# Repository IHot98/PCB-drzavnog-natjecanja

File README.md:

PCB drzavnog natjecanja
---
Za zadatak natjecanja bilo je potrebno izraditi robota (programranje, 3D dizajn i PCB)

Moj zadatak je bilo crtanje PCB-a i ovo je rezultat toga
 
 Za crtanje PCB-a bilo je zadana shema i ograničenja / dimenzije same pločice te koje se komponente moraju koristiti (kućišta)

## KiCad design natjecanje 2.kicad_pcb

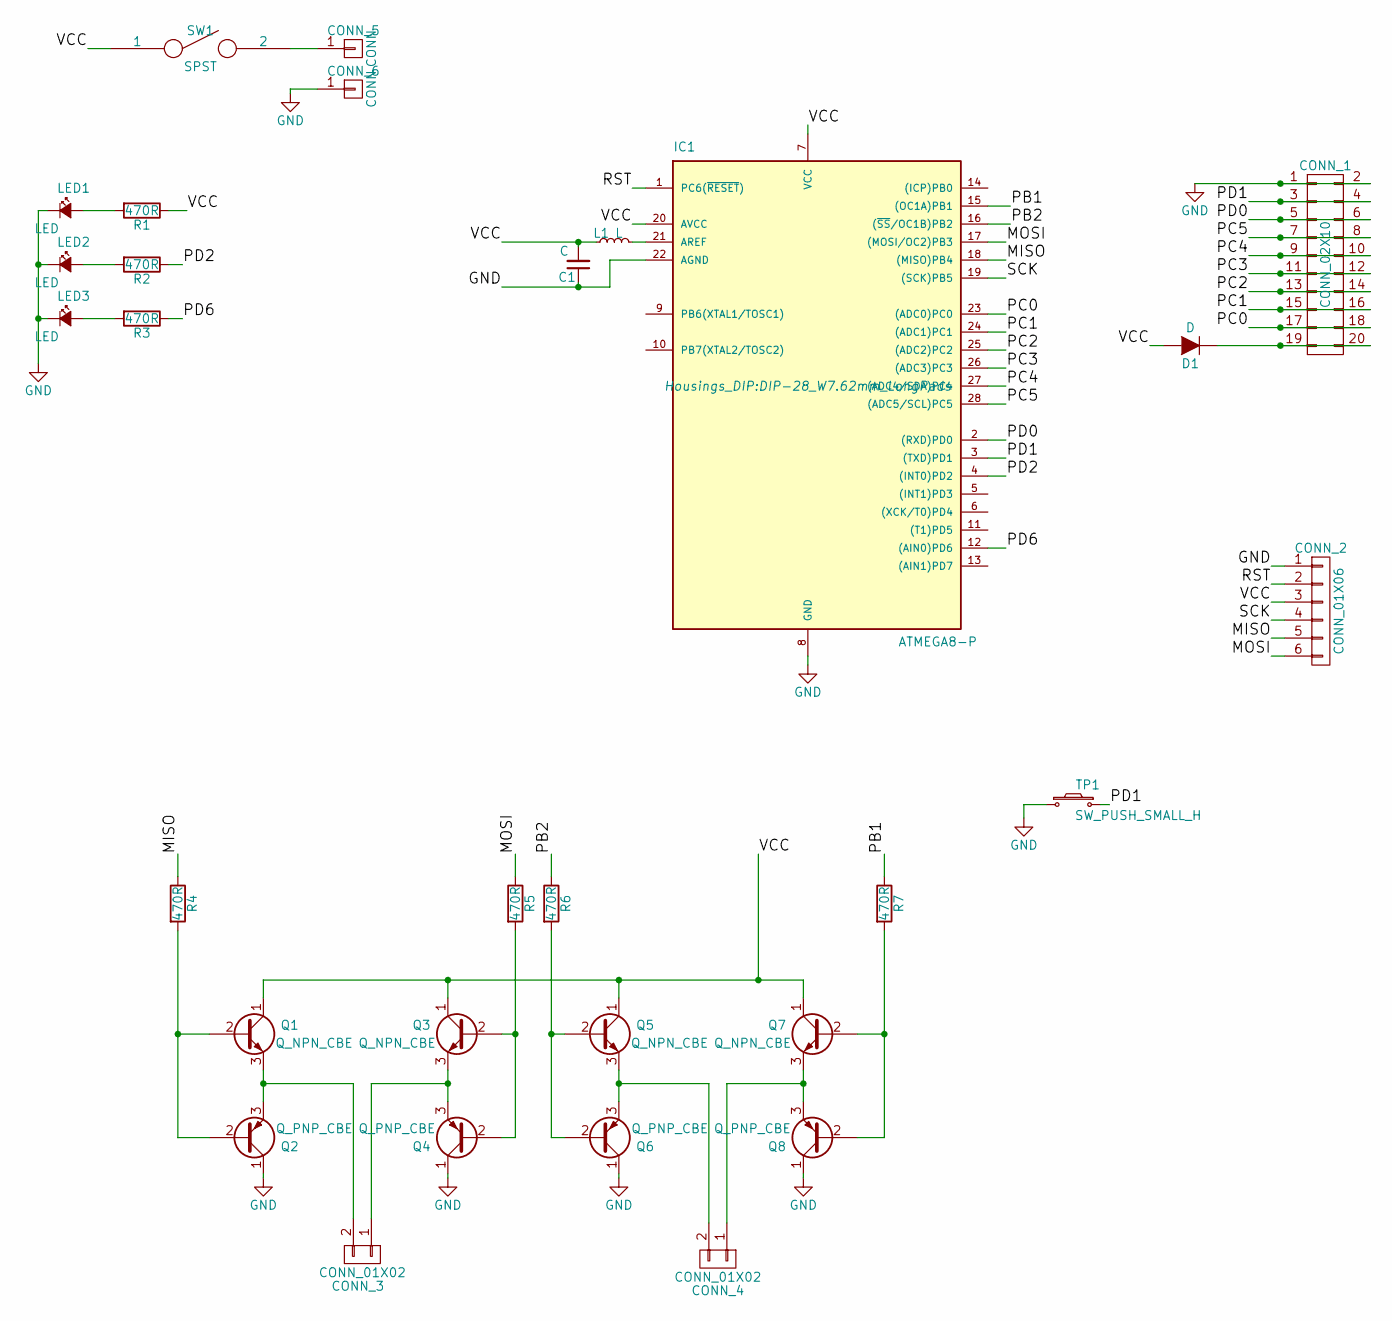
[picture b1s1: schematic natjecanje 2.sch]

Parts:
C1: C; C_Rect_L7.2mm_W2.5mm_P5.00mm_FKS2_FKP2_MKS2_MKP2
CONN_1: CONN_02X10; Pin_Header_Angled_2x10_Pitch2.54mm
CONN_2: CONN_01X06; Pin_Header_Straight_1x06_Pitch2.54mm
CONN_3, CONN_4: CONN_01X02; Pin_Header_Straight_1x02_Pitch2.54mm
CONN_5, CONN_6: CONN; Pin_Header_Straight_1x01_Pitch2.54mm
D1: D; Diode_DO-35_SOD27_Horizontal_RM10
IC1: ATMEGA8-P; DIP-28_W7.62mm_LongPads
L1: L; L_Axial_L5.3mm_D2.2mm_P10.16mm_Horizontal_Vishay_IM-1
LED1, LED2, LED3: LED; LED_D3.0mm
Q1, Q3, Q5, Q7: Q_NPN_CBE; TO-92_Inline_Wide
Q2, Q4, Q6, Q8: Q_PNP_CBE; TO-92_Inline_Wide
R1, R2, R3, R4, R5, R6, R7: 470R; Resistor_Horizontal_RM10mm
SW1: SPST; SW_DIP_x1_W7.62mm_Slide_LowProfile
TP1: SW_PUSH_SMALL_H; SW_PUSH_6mm_h4.3mm

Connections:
/MISO: CONN_2.5, IC1.18 ((MISO)PB4), R4.1
/MOSI: CONN_2.6, IC1.17 ((MOSI/OC2)PB3), R5.1
/PB1: IC1.15 ((OC1A)PB1), R7.1
/PB2: IC1.16 ((~SS~/OC1B)PB2), R6.1
/PC0: CONN_1.17, CONN_1.18, IC1.23 ((ADC0)PC0)
/PC1: CONN_1.15, CONN_1.16, IC1.24 ((ADC1)PC1)
/PC2: CONN_1.13, CONN_1.14, IC1.25 ((ADC2)PC2)
/PC3: CONN_1.11, CONN_1.12, IC1.26 ((ADC3)PC3)
/PC4: CONN_1.9, CONN_1.10, IC1.27 ((ADC4/SDA)PC4)
/PC5: CONN_1.7, CONN_1.8, IC1.28 ((ADC5/SCL)PC5)
/PD0: CONN_1.5, CONN_1.6, IC1.2 ((RXD)PD0)
/PD1: CONN_1.3, CONN_1.4, IC1.3 ((TXD)PD1), TP1.2
/PD2: IC1.4 ((INT0)PD2), R2.1
/PD6: IC1.12 ((AIN0)PD6), R3.1
/RST: CONN_2.2, IC1.1 (PC6(~RESET~))
/SCK: CONN_2.4, IC1.19 ((SCK)PB5)
/VCC: C1.2, CONN_2.3, D1.2 (A), IC1.7 (VCC), IC1.20 (AVCC), L1.1, Q1.1 (C), Q3.1 (C), Q5.1 (C), Q7.1 (C), R1.1, SW1.1
GND: C1.1, CONN_1.1, CONN_1.2, CONN_2.1, CONN_6.1, IC1.8 (GND), IC1.22 (AGND), LED1.1 (K), LED2.1 (K), LED3.1 (K), Q2.1 (C), Q4.1 (C), Q6.1 (C), Q8.1 (C), TP1.1
unnamed: CONN_1.19, CONN_1.20, D1.1 (K)
unnamed: CONN_3.1, Q3.3 (E), Q4.3 (E)
unnamed: CONN_3.2, Q1.3 (E), Q2.3 (E)
unnamed: CONN_4.1, Q7.3 (E), Q8.3 (E)
unnamed: CONN_4.2, Q5.3 (E), Q6.3 (E)
unnamed: CONN_5.1, SW1.2
unnamed: IC1.21 (AREF), L1.2
unnamed: LED1.2 (A), R1.2
unnamed: LED2.2 (A), R2.2
unnamed: LED3.2 (A), R3.2
unnamed: Q1.2 (B), Q2.2 (B), R4.2
unnamed: Q3.2 (B), Q4.2 (B), R5.2
unnamed: Q5.2 (B), Q6.2 (B), R6.2
unnamed: Q7.2 (B), Q8.2 (B), R7.2

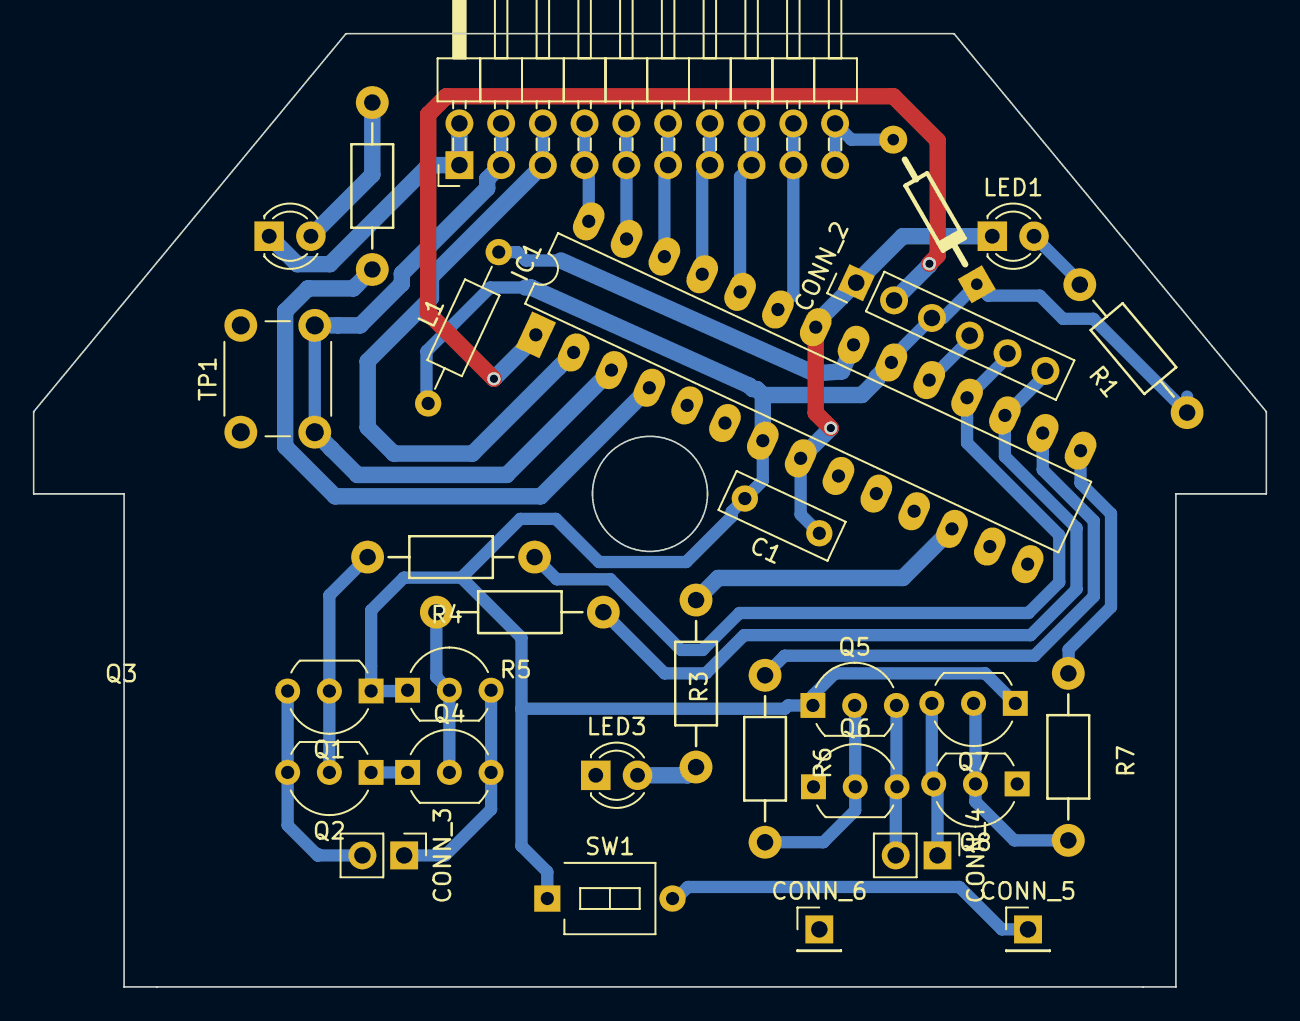
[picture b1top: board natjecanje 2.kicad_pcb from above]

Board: 2 copper layers, 75.0 x 58.0 mm, 30 parts (0 on the bottom side), 32 nets.
